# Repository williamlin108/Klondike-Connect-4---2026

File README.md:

# Klondike Connect 4 — Electronics
*README generated based on internal 10/9/2026 midterm design review PowerPoint content*

Electronics and firmware for the semi-automatic giant Connect 4 board built by EPICS at Purdue (Fall 2026) for Klondike Elementary School. A motorized rack-and-pinion slider releases the game pieces at the end of a round, and addressable LEDs plus a Wi-Fi web interface add interactive control.

## Features

- **Automatic reset:** a stepper-driven slider under the board lines up its holes with the columns so the pieces drop out
- **Wireless control:** the ESP32 hosts a local Wi-Fi access point and a web control page
- **Addressable RGBW LEDs:** two independent LED channels driven in real time by the STM32
- **Safety:** endstop and motor-stall hardware interrupts stop the slider immediately

## System Overview

```
AC/DC (Mean Well) ──+24V──► TMC2209 ──4-wire──► NEMA17 stepper (rack & pinion)
        │
        └──+5V──► LED strips (A, B)
                └─► Buck converter ──+3V3──► STM32G431 ◄──UART──► ESP32-C3 ──Wi-Fi──► Web control app
                                                 ▲
                                    Endstops A/B, TMC DIAG (interrupts)
```

## Hardware

| Block | Part | Role |
|---|---|---|
| Main controller | STM32G431CBT6 (LQFP48) | LED rendering, motor control, interrupts |
| Wireless link | ESP32-C3 module | Wi-Fi access point, web UI, remote updates of the STM32 firmware |
| Motor driver | Trinamic TMC2209 | Quiet stepper drive (STEP/DIR + UART), stall detection |
| Motor | NEMA17 stepper | Drives the slider through a rack and pinion |
| Logic power | Buck converter, 5V → 3V3 | Powers STM32 and ESP32 |
| Power supplies | Mean Well AC/DC (+5V LED/logic, +24V motor) | Pre-certified, protected mains conversion |
| Homing | 2× microswitch endstops | Double-endstop slider limits |
| LEDs | Adafruit NeoPixel RGBW strips | Board lighting |

### Connectors

| Connector | Description |
|---|---|
| J1 — +5V input | Main power for LEDs and logic; fused (6A) with TVS protection |
| J2 — +24V input | Motor power only |
| J3 / J4 — EndA / EndB | Slider endstops |
| J5 / J6 — LEDA / LEDB | 3-pin LED outputs (Data, +5V, GND), each fused at 2A |
| J7 — MOTOR | 4-wire stepper (two coil pairs) |
| USB-C | Flash the ESP32; ESD protected |
| TC2030 | SWD programming for the STM32 |

### STM32 Pin Map

> Taken from the CubeMX pinout; verify against the KiCad schematic before writing firmware.

| Signal | Pin |
|---|---|
| LEDA data | PA8 |
| LEDB data | PA9 |
| EndA / EndB | PB13 / PB14 |
| InterA / InterB | PB11 / PB12 |
| TMC_STEP / TMC_DIR | PA5 / PA6 |
| TMC_EN | PA4 |
| TMC_DIAG | PA3 |
| TMC_PDN (UART) | PA2 |
| ESP32 UART | PB6 / PB7 |
| SWDIO / SWCLK | PA13 / PA14 |

## Firmware

| Component | Choice | Why |
|---|---|---|
| MCU | STM32 + ESP32 | Best score for documentation, performance, reliability |
| RTOS | Zephyr | Documentation and maintainability |
| Homing | Double endstop | Reliability |

### LED Protocol

- 800 kHz, 1.25 µs per bit
- `0` = 0.3 µs high / 0.9 µs low; `1` = 0.6 µs high / 0.6 µs low
- 32 bits per LED (GRBW, MSB first) = 40 µs per LED
- Hold low ≥ 80 µs after the last LED to latch
- Each LED takes its own packet and passes the rest down the chain

### Interrupts

- **Endstops:** fire when the slider reaches either end; the controller halts and runs the handler
- **TMC2209 DIAG:** fires on abnormal load (stall), stopping the motor

### Web Interface (ESP32)

The ESP32 starts a soft access point and serves a control page on port 80. Connect to the `KlondikeESP32` network and open the IP printed on the serial monitor (115200 baud). The current prototype toggles an LED via `GET /H` and `GET /L`.

## Repository Layout

```
hardware/    KiCad schematic, PCB layout, BOM
firmware/
  stm32/     Zephyr application and device tree drivers
  esp32/     Access point and web control page
docs/        Wiring diagrams and user manual
```

## Getting Started

1. Wire the Mean Well supplies to J1 (+5V) and J2 (+24V).
2. Flash the ESP32 over USB-C.
3. Flash the STM32 over SWD (TC2030), or remotely through the ESP32.
4. Connect to `KlondikeESP32` Wi-Fi and open the control page.
5. Home the slider against the endstops before the first game.

## Status

- [x] Electronics specification, schematic, PCB layout
- [x] ESP32 web control prototype
- [x] PCB fabrication (ordered)
- [ ] Firmware (device tree drivers in progress)
- [ ] Mechanical + electrical integration
- [ ] Validation testing and delivery (early December 2026)

## Team

**Electrical:** William Lin (Design Lead), Ram Vadhadia (Project Archivist), Alani Martinez (Financial Officer)

**Mechanical:** Robert Thomas (Design Lead), Max Siesky (Project Manager), Adler Torchia (Financial Officer), Sarah Doerich (Communications Officer), Chris Ferranti

EPICS at Purdue · Project partner: Klondike Elementary School

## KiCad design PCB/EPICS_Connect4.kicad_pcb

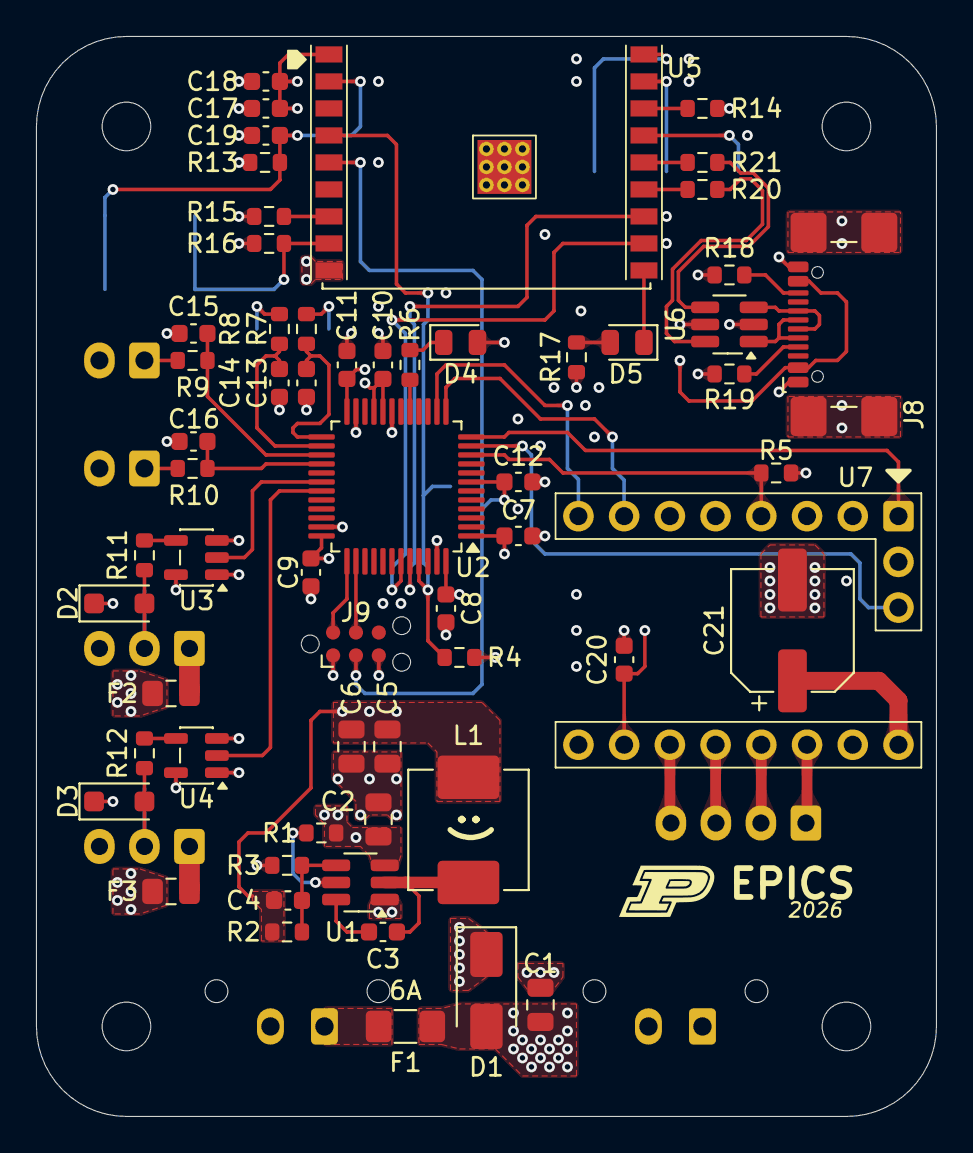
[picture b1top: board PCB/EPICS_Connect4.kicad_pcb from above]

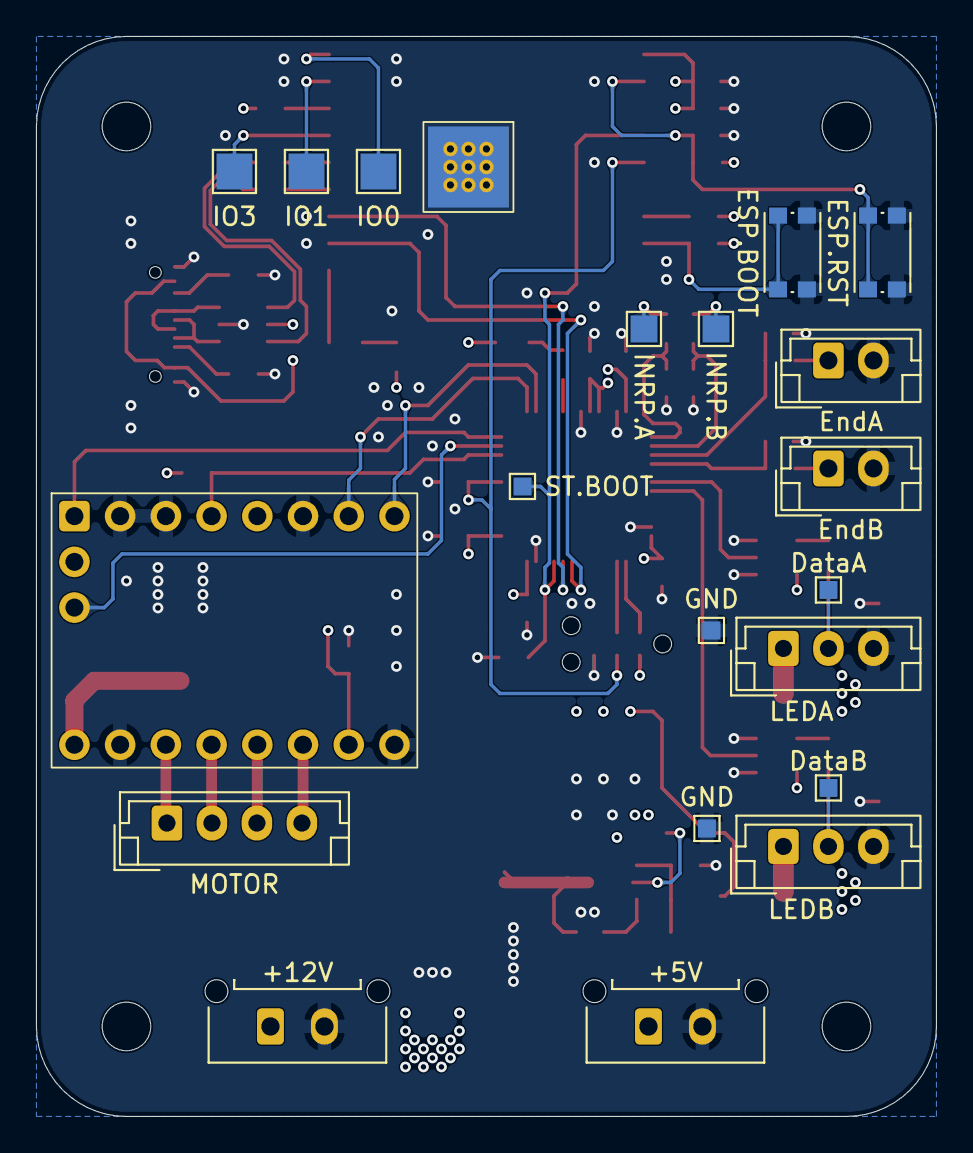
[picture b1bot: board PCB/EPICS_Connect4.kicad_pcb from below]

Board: 4 copper layers, 50.0 x 60.0 mm, 84 parts (19 on the bottom side), 60 nets.

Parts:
C1, C2, C5, C6: 22uF; C_0805_2012Metric
C3, C12, C13, C14, C15, C16: 0.1uF; C_0603_1608Metric
C4: 56pF; C_0603_1608Metric
C7, C8, C9, C10, C11, C19, C20: 1uF; C_0603_1608Metric
C17, C18: 10uF; C_0603_1608Metric
C21: 100uF; CP_Elec_6.3x5.9
D1: SMAJ5A; D_SMA
D2, D3: SMF5.0A; D_SOD-123F
D4, D5: 4.5mA @ 1.8V; LED_0805_2012Metric
F1: 6A; Fuse_1206_3216Metric_Pad1.42x1.75mm_HandSolder
F2, F3: 2A; Fuse_0805_2012Metric_Pad1.15x1.40mm_HandSolder
H1, H2, H3, H4: MountingHole; MountingHole_2.7mm_M2.5
J1: +5V; Molex_Micro-Fit_3.0_43650-0215_1x02_P3.00mm_Vertical
J2: +12V; Molex_Micro-Fit_3.0_43650-0215_1x02_P3.00mm_Vertical
J3: EndA; JST_EH_B2B-EH-A_1x02_P2.50mm_Vertical
J4: EndB; JST_EH_B2B-EH-A_1x02_P2.50mm_Vertical
J5: LEDA; JST_EH_B3B-EH-A_1x03_P2.50mm_Vertical
J6: LEDB; JST_EH_B3B-EH-A_1x03_P2.50mm_Vertical
J7: MOTOR; JST_EH_B4B-EH-A_1x04_P2.50mm_Vertical
J8: USB_C_Receptacle_USB2.0_14P; USB_C_Receptacle_GCT_USB4110
J9: TC2030; Tag-Connect_TC2030-IDC-NL_2x03_P1.27mm_Vertical
L1: 10uH; L_Vishay_IHLP-2525
R1: 510k; R_0603_1608Metric
R2: 100k; R_0603_1608Metric
R3: 22.1k; R_0603_1608Metric
R4, R13, R14, R15, R16: 10k; R_0603_1608Metric
R5, R18, R19: 5.1k; R_0603_1608Metric
R6, R7, R8, R9, R10, R11, R12, R17: 330; R_0603_1608Metric
R20, R21: 22; R_0603_1608Metric
SW1: ESP.RST; SW_Push_1P1T_NO_CK_KMR2
SW2: ESP.BOOT; SW_Push_1P1T_NO_CK_KMR2
SYM1: Logo_Open_Hardware_Large; S_Silk_Logo
TP1: ST.BOOT; TestPoint_Pad_1.0x1.0mm
TP2, TP4: GND; TestPoint_Pad_1.0x1.0mm
TP3: DataA; TestPoint_Pad_1.0x1.0mm
TP5: DataB; TestPoint_Pad_1.0x1.0mm
TP6: IO0; TestPoint_Pad_2.0x2.0mm
TP7: IO1; TestPoint_Pad_2.0x2.0mm
TP8: IO3; TestPoint_Pad_2.0x2.0mm
TP9: INRP.A; TestPoint_Pad_1.5x1.5mm
TP10: INRP.B; TestPoint_Pad_1.5x1.5mm
U1: TPS54202DDC; SOT-23-6_Handsoldering
U2: STM32G474CBTx; LQFP-48_7x7mm_P0.5mm
U3, U4: SN74AHCT1G125DBVR; SOT-23-5
U5: ESP32-C3-WROOM-02; ESP32-C3-WROOM-02_Modified
U6: USBLC6-2SC6; SOT-23-6_Handsoldering
U7: TMC2209; STEPSTICK_socket

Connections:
+3V3: C4.2, C5.2, C6.2, C7.1, C8.1, C9.1, C10.1, C11.1, C17.1, C18.1, C20.2, D4.2 (A), J9.1, L1.2, R2.1, R5.1, R13.1, R14.1, R15.1, R16.1, R17.1, U2.1 (VBAT), U2.20 (VREF+), U2.21 (VDDA), U2.24 (VDD), U2.36 (VDD), U2.48 (VDD), U5.1 (3V3), U7.15 (VIO)
+5V: C1.1, C2.2, D1.2 (A2), F1.2, F2.1, F3.1, R1.1, U1.3 (VIN), U3.5 (VCC), U4.5 (VCC)
+12V: C21.1, J2.1, U7.9 (VM)
/ESP32 Weblink/D+: R21.2, U5.14 (IO19)
/ESP32 Weblink/D-: R20.2, U5.13 (IO18)
/ESP32 Weblink/D.+: R21.1, U6.4 (I/O2)
/ESP32 Weblink/D.-: R20.1, U6.6 (I/O1)
/ESP32 Weblink/EN: C19.1, R13.2, SW1.2, U5.2 (EN)
/ESP32 Weblink/IO0: TP6.1 (1_1), U5.18 (IO0)
/ESP32 Weblink/IO1: TP7.1 (1_1), U5.17 (IO1)
/ESP32 Weblink/IO2: R14.2, U5.16 (IO2)
/ESP32 Weblink/IO3: TP8.1 (1_1), U5.15 (IO3)
/ESP32 Weblink/IO8: R15.2, U5.7 (IO8)
/ESP32 Weblink/IO9: R16.2, SW2.2, U5.8 (IO9)
/ESP32 Weblink/IO20/RXD: U2.43 (PB6), U5.11 (IO20/RXD)
/ESP32 Weblink/IO21/TXD: U2.44 (PB7), U5.12 (IO21/TXD)
/ESP32 Weblink/LED: D5.1 (K), U5.10 (IO10)
/Motor Acuator/M10: J7.1, U7.11 (A1)
/Motor Acuator/M11: J7.2, U7.12 (A2)
/Motor Acuator/M12: J7.3, U7.13 (B1)
/Motor Acuator/M13: J7.4, U7.14 (B2)
/Motor Acuator/TMC.DIAG: U2.11 (PA3), U7.R (DIAG)
/Motor Acuator/TMC.DIR: U2.14 (PA6), U7.8 (DIR)
/Motor Acuator/TMC.EN: U2.12 (PA4), U7.1 (EN)
/Motor Acuator/TMC.PDN: R5.2, U2.10 (PA2), U7.4 (PDN)
/Motor Acuator/TMC.STEP: U2.13 (PA5), U7.7 (STEP)
/STM32 Controller/BOOT: R4.1, TP1.1 (1_1), U2.45 (PB8), U5.4 (IO5)
/STM32 Controller/END.A: J3.1, R9.1
/STM32 Controller/END.A*: C15.1, R9.2, U2.27 (PB13)
/STM32 Controller/END.B: J4.1, R10.1
/STM32 Controller/END.B*: C16.1, R10.2, U2.28 (PB14)
/STM32 Controller/INRP.A: R7.1, TP9.1 (1_1)
/STM32 Controller/INRP.A*: C13.1, R7.2, U2.25 (PB11)
/STM32 Controller/INRP.B: R8.1, TP10.1 (1_1)
/STM32 Controller/INRP.B*: C14.1, R8.2, U2.26 (PB12)
/STM32 Controller/LED.A: U2.30 (PA8), U3.2 (A)
/STM32 Controller/LED.B: U2.31 (PA9), U4.2 (A)
/STM32 Controller/NRST: C12.1, J9.3, U2.7 (PG10), U5.5 (IO6)
/STM32 Controller/SWCLK: J9.4, U2.38 (PA14)
/STM32 Controller/SWDIO: J9.2, U2.37 (PA13)
/STM32 Controller/U_LED: R6.2, U2.17 (PB1)
/STM32 Controller/ledDataA: D2.2 (A2), J5.2, R11.2, TP3.1 (1_1)
/STM32 Controller/ledDataB: D3.2 (A2), J6.2, R12.2, TP5.1 (1_1)
GND: C1.2, C2.1, C5.1, C6.1, C7.2, C8.2, C9.2, C10.2, C11.2, C12.2, C13.2, C14.2, C15.2, C16.2, C17.2, C18.2, C19.2, C20.1, C21.2, D1.1 (A1), D2.1 (A1), D3.1 (A1), J1.2, J2.2, J3.2, J4.2, J5.3, J6.3, J8.A1 (GND), J8.A12 (GND), J8.B1 (GND), J8.B12 (GND), J8.SH (SHIELD), J9.5, R3.2, R4.2, R18.2, R19.2, SW1.1, SW2.1, TP2.1 (1_1), TP4.1 (1_1), U1.1 (GND), U2.19 (VSSA), U2.23 (VSS), U2.35 (VSS), U2.47 (VSS), U3.1 (~OE), U3.3 (GND), U4.1 (~OE), U4.3 (GND), U5.9 (GND), U5.19 (GND), U6.2 (GND), U7.2 (MS1), U7.3 (MS2), U7.6 (CLK), U7.10 (GND), U7.16 (GND)
unnamed: D4.1 (K), R6.1
unnamed: D5.2 (A), R17.2
unnamed: F1.1, J1.1
unnamed: F2.2, J5.1
unnamed: F3.2, J6.1
unnamed: J8.A5 (CC1), R19.1
unnamed: J8.B5 (CC2), R18.1
unnamed: J8.A6 (D+), J8.B6 (D+), U6.3 (I/O2)
unnamed: J8.A7 (D-), J8.B7 (D-), U6.1 (I/O1)
unnamed: C3.1, U1.6 (BOOT)
unnamed: R1.2, U1.5 (EN)
unnamed: C4.1, R2.2, R3.1, U1.4 (FB)
unnamed: C3.2, L1.1, U1.2 (SW)
unnamed: R11.1, U3.4 (Y)
unnamed: R12.1, U4.4 (Y)
unnamed: J8.A4 (VBUS), J8.A9 (VBUS), J8.B4 (VBUS), J8.B9 (VBUS), U6.5 (VBUS)

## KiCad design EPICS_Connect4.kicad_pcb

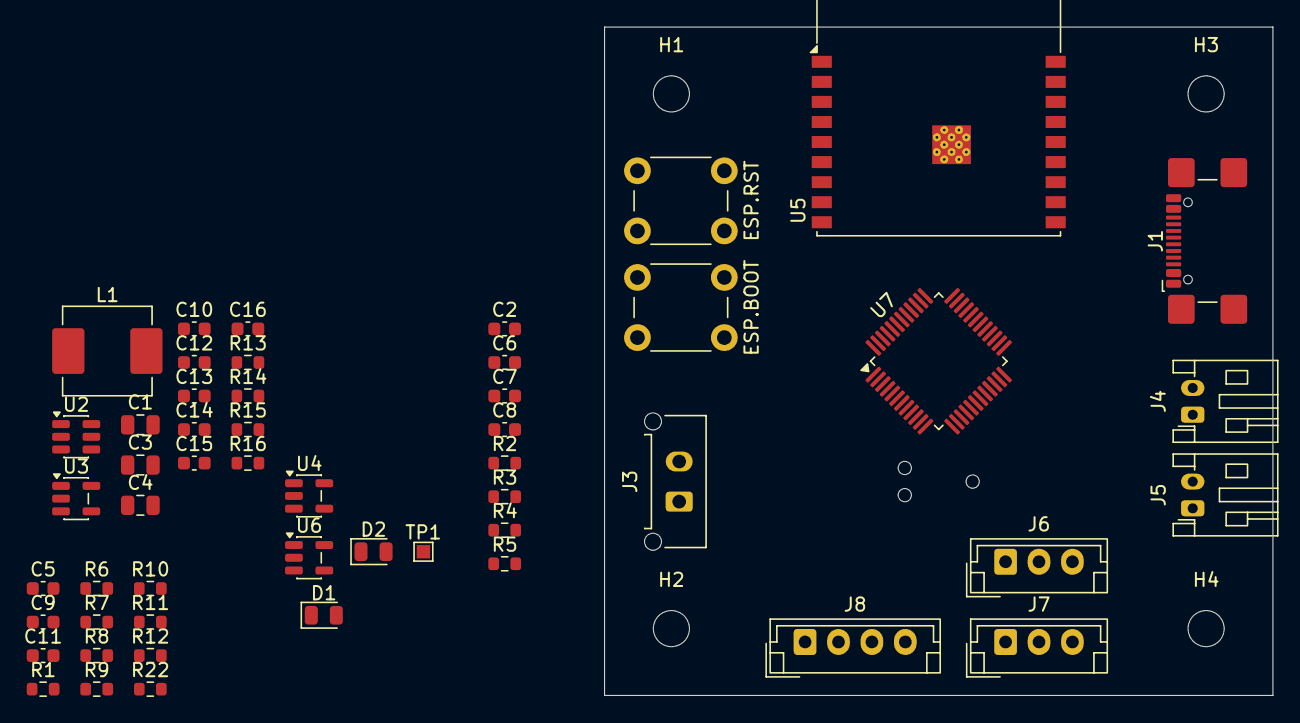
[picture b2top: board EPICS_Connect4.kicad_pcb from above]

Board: 2 copper layers, 50.0 x 50.0 mm, 57 parts (1 on the bottom side), 32 nets, no tracks yet.

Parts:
C1: 10uF; C_0805_2012Metric
C2, C16: 0.1uF; C_0603_1608Metric
C3, C4: 22uF; C_0805_2012Metric
C5, C6, C10, C12, C13, C14, C15: 1uF; C_0603_1608Metric
C7, C9, C11: 10uF; C_0603_1608Metric
C8: 56pF; C_0603_1608Metric
D1, D2: 4.5mA @ 1.8V; LED_0805_2012Metric
H1, H2, H3, H4: MountingHole; MountingHole_2.7mm_M2.5
J1: USB_C_Receptacle_USB2.0_14P; USB_C_Receptacle_GCT_USB4110
J2: TC2030; Tag-Connect_TC2030-IDC-NL_2x03_P1.27mm_Vertical
J3: Power; Molex_Micro-Fit_3.0_43650-0215_1x02_P3.00mm_Vertical
J4: EndA; JST_PH_S2B-PH-K_1x02_P2.00mm_Horizontal
J5: EndB; JST_PH_S2B-PH-K_1x02_P2.00mm_Horizontal
J6: LEDA; JST_EH_B3B-EH-A_1x03_P2.50mm_Vertical
J7: LEDB; JST_EH_B3B-EH-A_1x03_P2.50mm_Vertical
J8: Motor; JST_EH_B4B-EH-A_1x04_P2.50mm_Vertical
L1: 10uH; L_Vishay_IHLP-2525
R1, R11, R22: 5.1k; R_0603_1608Metric
R2: 22.1k; R_0603_1608Metric
R3: 330k; R_0603_1608Metric
R4: 100k; R_0603_1608Metric
R5: 56k; R_0603_1608Metric
R6, R15: 330; R_0603_1608Metric
R7, R8, R9, R10, R16: 10k; R_0603_1608Metric
R12: 22; R_0603_1608Metric
R13, R14: 75; R_0603_1608Metric
SW1: ESP.RST; SW_PUSH_6mm_H4.3mm
SW2: ESP.BOOT; SW_PUSH_6mm_H4.3mm
TP1: ST.BOOT; TestPoint_Pad_1.0x1.0mm
U2: TPS54202DDC; SOT-23-6
U3: AP2205-5; SOT-23-5
U4, U6: SN74AHCT1G125DBVR; SOT-23-5
U5: ESP32-C3-WROOM-02
U7: STM32G474CBTx; LQFP-48_7x7mm_P0.5mm

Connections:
+3V3: C9.1, C10.1, C11.1, C12.1, C13.1, C14.1, C15.1, J2.1, R6.1, R7.1, R8.1, R9.1, R10.1, R15.1, U5.1 (3V3), U7.1 (VBAT), U7.20 (VREF+), U7.21 (VDDA), U7.24 (VDD), U7.36 (VDD), U7.48 (VDD)
+5V: U4.5 (VCC), U6.5 (VCC)
/ESP32 Weblink/D+: R22.2, U5.14 (IO19)
/ESP32 Weblink/D-: R12.2, U5.13 (IO18)
/ESP32 Weblink/EN: C5.1, R9.2, SW1.2, U5.2 (EN)
/ESP32 Weblink/IO2: R7.2, U5.16 (IO2)
/ESP32 Weblink/IO8: R10.2, U5.7 (IO8)
/ESP32 Weblink/IO9: R8.2, SW2.2, U5.8 (IO9)
/ESP32 Weblink/LED: D1.1 (K), U5.10 (IO10)
/Power Regulators/+3V3: C3.2, C4.2, C8.2, L1.2, R4.1
/Power Regulators/+5V: C7.2, U3.5 (VOUT)
/Power Regulators/EN: R3.2, R5.1, U2.5 (EN)
/Power Regulators/VIN: C1.2, C6.2, R3.1, U2.3 (VIN), U3.1 (VIN), U3.3 (EN)
/STM32 Controller/BOOT: R16.1, TP1.1 (1_1), U7.45 (PB8)
/STM32 Controller/LED.A: U4.2 (A), U7.30 (PA8)
/STM32 Controller/LED.B: U6.2 (A), U7.31 (PA9)
/STM32 Controller/NRST: C16.1, J2.3, U7.7 (PG10)
/STM32 Controller/SWCLK: J2.4, U7.38 (PA14)
/STM32 Controller/SWDIO: J2.2, U7.37 (PA13)
/STM32 Controller/U_LED: D2.1 (K), U7.33 (PA11)
GND: C1.1, C3.1, C4.1, C5.2, C6.1, C7.1, C9.2, C10.2, C11.2, C12.2, C13.2, C14.2, C15.2, C16.2, J1.A1 (GND), J1.A12 (GND), J1.B1 (GND), J1.B12 (GND), J1.SH (SHIELD), J2.5, R1.2, R2.2, R5.2, R11.2, R16.2, SW1.1, SW2.1, U2.1 (GND), U3.2 (GND), U4.1 (~OE), U4.3 (GND), U5.9 (GND), U5.19 (GND), U6.1 (~OE), U6.3 (GND), U7.19 (VSSA), U7.23 (VSS), U7.35 (VSS), U7.47 (VSS)
unnamed: D1.2 (A), R6.2
unnamed: D2.2 (A), R15.2
unnamed: J1.A5 (CC1), R1.1
unnamed: J1.B5 (CC2), R11.1
unnamed: J1.A6 (D+), J1.B6 (D+), R22.1
unnamed: J1.A7 (D-), J1.B7 (D-), R12.1
unnamed: C2.1, U2.6 (BOOT)
unnamed: C8.1, R2.1, R4.2, U2.4 (FB)
unnamed: C2.2, L1.1, U2.2 (SW)
unnamed: R13.1, U4.4 (Y)
unnamed: R14.1, U6.4 (Y)
